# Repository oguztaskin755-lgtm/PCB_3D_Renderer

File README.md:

# PCB_3D_Renderer

THIS PROJECT AND README IS WORK IN PROGRESS AND NOT FINISHED

Currently the PCB is done and only the firmware is not finished.

A PCB with STM32 and SSD1306 to display 3D objects using a 3D Renderer that I made.

# Hardware

I used a 4 layer PCB with top and bottom layers being signal plane and inner layer 1 being GND plane (Both analog and digital) and inner layer 2 being +3.3V plane (Both analog and digital)

The project uses a STM32F301C8T6 MCU and a SSD1306 128x64 single color display.

# Software

The project is being programmed in bare metal using C. Currently the software is not complete.

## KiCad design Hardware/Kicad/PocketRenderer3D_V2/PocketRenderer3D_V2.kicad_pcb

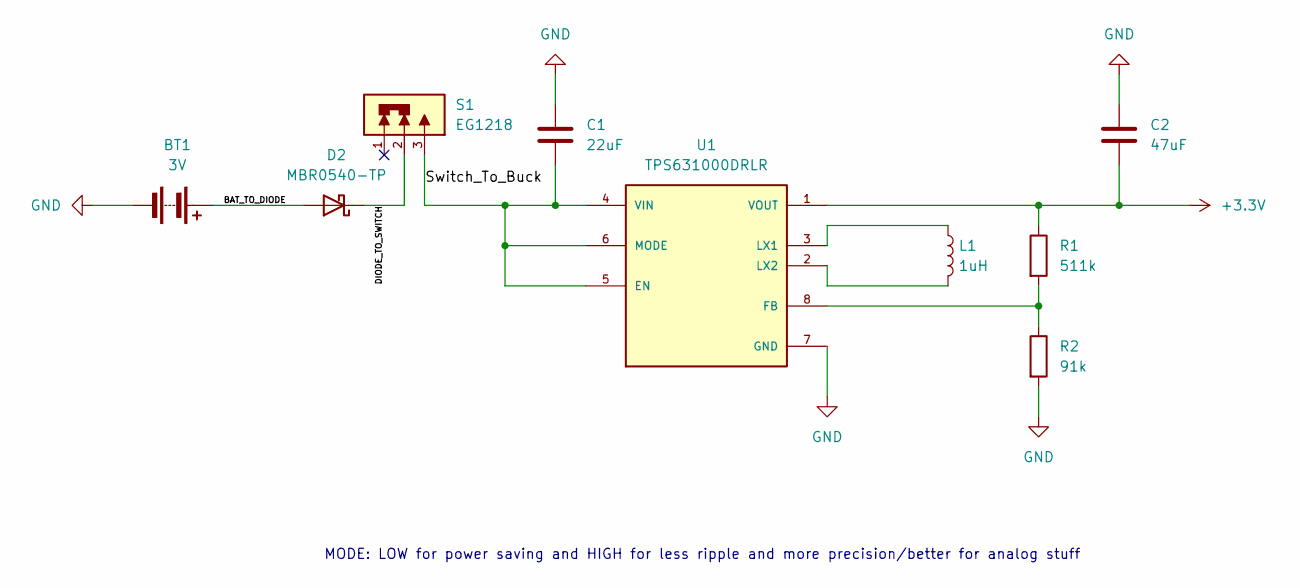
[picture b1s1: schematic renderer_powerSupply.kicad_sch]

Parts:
BT1: 3V; BatteryHolder_Keystone_1060_1x2032
C1: 22uF; C_0603_1608Metric_Pad1.08x0.95mm_HandSolder
C2: 47uF; C_0805_2012Metric_Pad1.18x1.45mm_HandSolder
D2: MBR0540-TP; D_SOD-123
L1: 1uH; L_0603_1608Metric_Pad1.05x0.95mm_HandSolder
R1: 511k; R_0603_1608Metric_Pad0.98x0.95mm_HandSolder
R2: 91k; R_0603_1608Metric_Pad0.98x0.95mm_HandSolder
S1: EG1218; SW_EG1218
U1: TPS631000DRLR; SOT50P160X60-8N; PARTREV B

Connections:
+3.3V: C2.2, R1.1, U1.1 (VOUT); also elsewhere on the board
/Renderer_PowerSupply/BAT_TO_DIODE: BT1.1 (+), D2.2 (A)
/Renderer_PowerSupply/DIODE_TO_SWITCH: D2.1 (K), S1.2
/Renderer_PowerSupply/Switch_To_Buck: C1.2, S1.3, U1.4 (VIN), U1.5 (EN), U1.6 (MODE)
GND: BT1.2 (-), C1.1, C2.1, R2.2, U1.7 (GND); also elsewhere on the board
unnamed: R1.2, R2.1, U1.8 (FB)
unnamed: L1.1, U1.3 (LX1)
unnamed: L1.2, U1.2 (LX2)

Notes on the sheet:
MODE: LOW for power saving and HIGH for less ripple and more precision/better for analog stuff

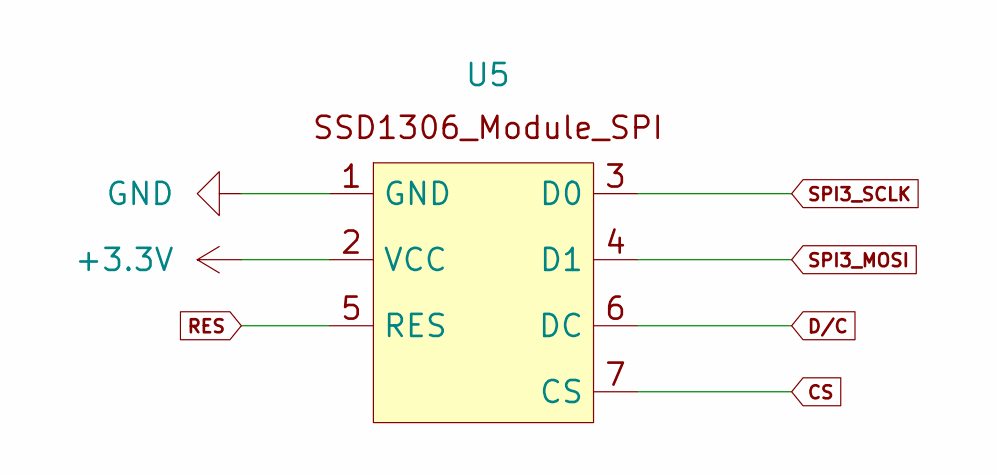
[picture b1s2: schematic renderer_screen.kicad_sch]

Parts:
U5: SSD1306; SSD1306_Module_SPI

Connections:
+3.3V: U5.2 (VCC); also elsewhere on the board
CS: U5.7 (CS); also elsewhere on the board
D/C: U5.6 (DC); also elsewhere on the board
GND: U5.1 (GND); also elsewhere on the board
RES: U5.5 (RES); also elsewhere on the board
SPI3_MOSI: U5.4 (D1); also elsewhere on the board
SPI3_SCLK: U5.3 (D0); also elsewhere on the board

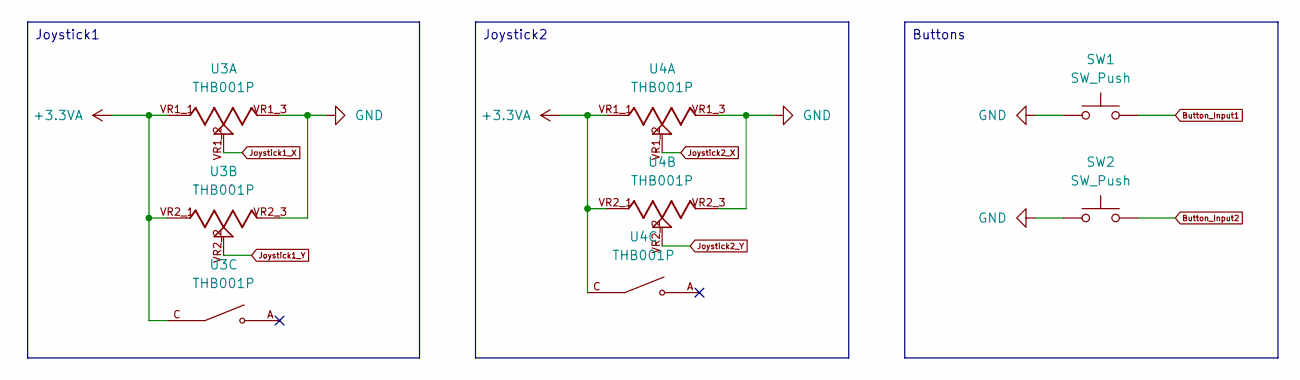
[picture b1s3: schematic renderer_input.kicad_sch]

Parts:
SW1, SW2: SW_Push; SW_PUSH_6mm_H4.3mm
U3, U4: THB001P; CNK_THB001P; PARTREV 27 Jan 22

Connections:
+3.3VA: U3.C, U3.D, U3.VR1_1, U3.VR2_1, U4.C, U4.D, U4.VR1_1, U4.VR2_1; also elsewhere on the board
Button_Input1: SW1.2; also elsewhere on the board
Button_Input2: SW2.2; also elsewhere on the board
GND: SW1.1, SW2.1, U3.VR1_3, U3.VR2_3, U4.VR1_3, U4.VR2_3; also elsewhere on the board
Joystick1_X: U3.VR1_2; also elsewhere on the board
Joystick1_Y: U3.VR2_2; also elsewhere on the board
Joystick2_X: U4.VR1_2; also elsewhere on the board
Joystick2_Y: U4.VR2_2; also elsewhere on the board

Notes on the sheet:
Joystick2
Buttons
Joystick1

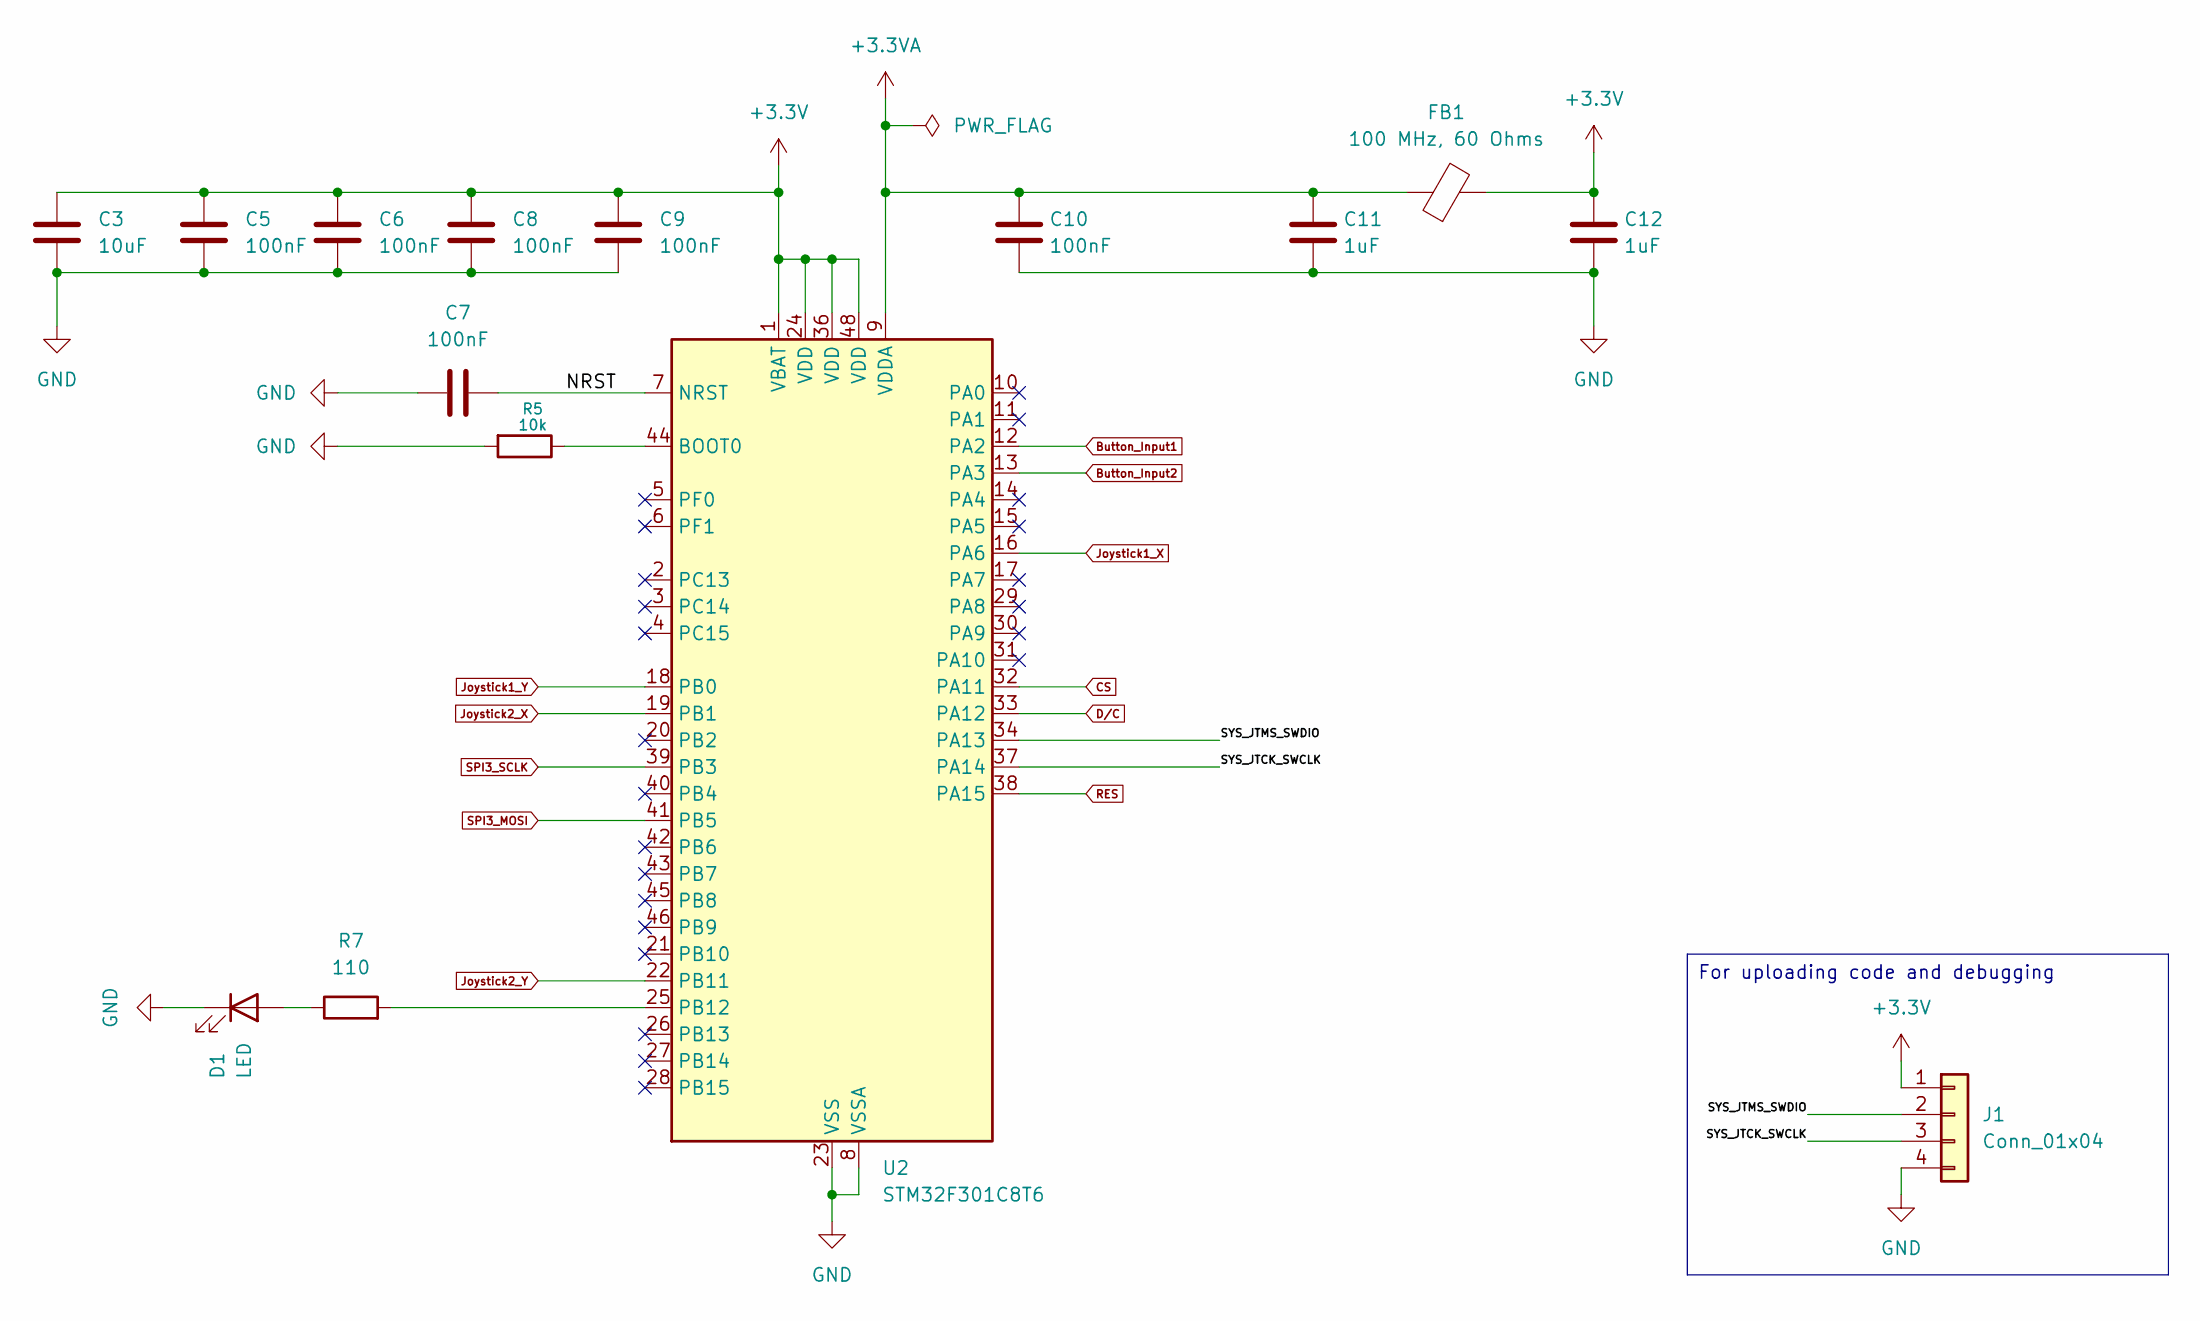
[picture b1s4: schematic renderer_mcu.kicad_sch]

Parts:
C3: 10uF; C_0805_2012Metric_Pad1.18x1.45mm_HandSolder
C5, C6, C7, C8, C9, C10: 100nF; C_0603_1608Metric_Pad1.08x0.95mm_HandSolder
C11, C12: 1uF; C_0603_1608Metric_Pad1.08x0.95mm_HandSolder
D1: LED; LED_D3.0mm
FB1: 100 MHz, 60 Ohms; L_0805_2012Metric_Pad1.05x1.20mm_HandSolder
J1: Conn_01x04; PinHeader_1x04_P2.54mm_Vertical
R5: 10k; R_0805_2012Metric_Pad1.20x1.40mm_HandSolder
R7: 110; R_0603_1608Metric_Pad0.98x0.95mm_HandSolder
U2: STM32F301C8T6; LQFP-48_7x7mm_P0.5mm

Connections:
+3.3V: C3.1, C5.2, C6.2, C8.2, C9.2, C12.2, FB1.2, J1.1, U2.1 (VBAT), U2.24 (VDD), U2.36 (VDD), U2.48 (VDD); also elsewhere on the board
+3.3VA: C10.2, C11.2, FB1.1, U2.9 (VDDA); also elsewhere on the board
/Render_MCU/NRST: C7.1, U2.7 (NRST)
/Render_MCU/SYS_JTCK_SWCLK: J1.3, U2.37 (PA14)
/Render_MCU/SYS_JTMS_SWDIO: J1.2, U2.34 (PA13)
Button_Input1: U2.12 (PA2); also elsewhere on the board
Button_Input2: U2.13 (PA3); also elsewhere on the board
CS: U2.32 (PA11); also elsewhere on the board
D/C: U2.33 (PA12); also elsewhere on the board
GND: C3.2, C5.1, C6.1, C7.2, C8.1, C9.1, C10.1, C11.1, C12.1, D1.1 (K), J1.4, R5.2, U2.8 (VSSA), U2.23 (VSS), U2.35 (VSS), U2.47 (VSS); also elsewhere on the board
Joystick1_X: U2.16 (PA6); also elsewhere on the board
Joystick1_Y: U2.18 (PB0); also elsewhere on the board
Joystick2_X: U2.19 (PB1); also elsewhere on the board
Joystick2_Y: U2.22 (PB11); also elsewhere on the board
unnamed: D1.2 (A), R7.1
unnamed: R5.1, U2.44 (BOOT0)
unnamed: R7.2, U2.25 (PB12)
RES: U2.38 (PA15); also elsewhere on the board
SPI3_MOSI: U2.41 (PB5); also elsewhere on the board
SPI3_SCLK: U2.39 (PB3); also elsewhere on the board

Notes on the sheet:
For uploading code and debugging

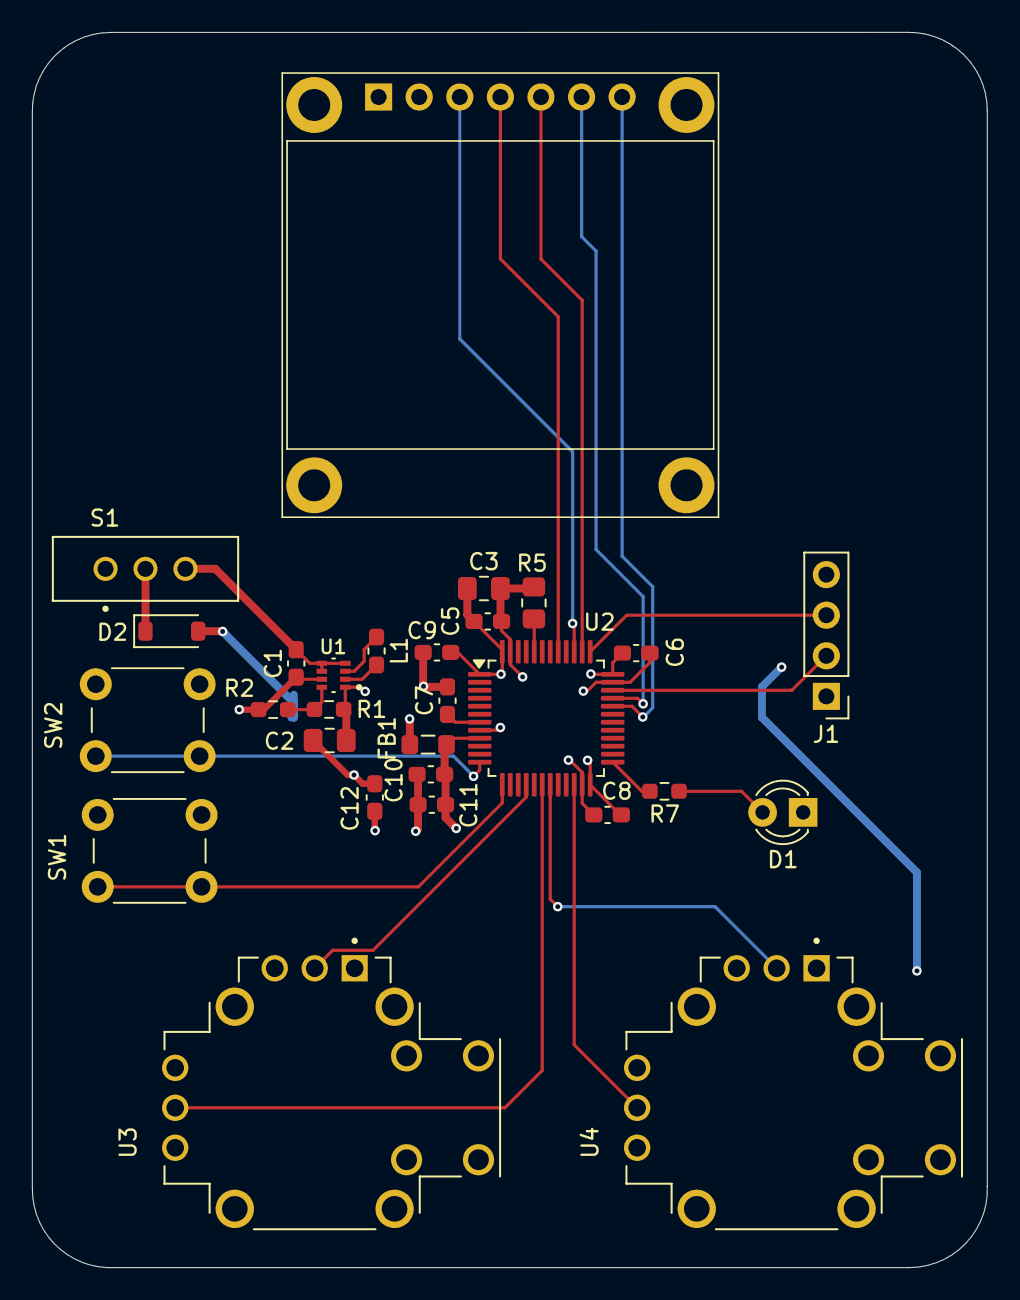
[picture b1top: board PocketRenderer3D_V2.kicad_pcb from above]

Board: 4 copper layers, 59.8 x 77.3 mm, 29 parts (1 on the bottom side), 26 nets.
